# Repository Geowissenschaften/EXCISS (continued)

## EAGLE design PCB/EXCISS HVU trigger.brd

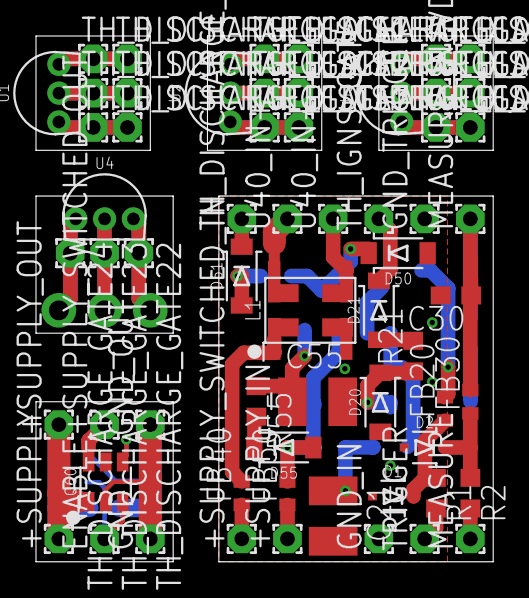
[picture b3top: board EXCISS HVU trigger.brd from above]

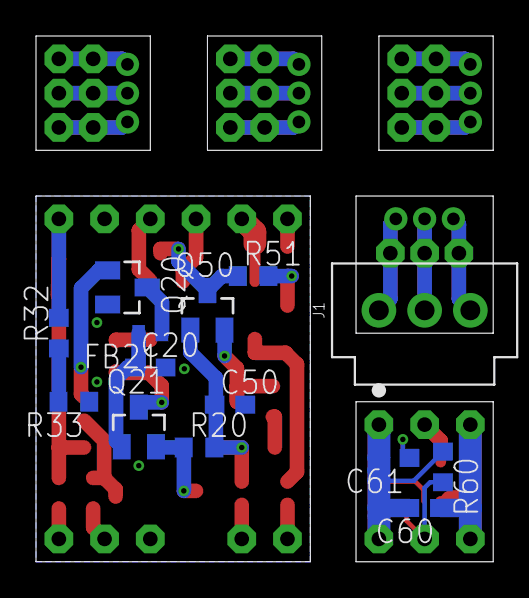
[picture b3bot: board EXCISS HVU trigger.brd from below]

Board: 2 copper layers, 25.4 x 29.2 mm, 76 parts (14 on the bottom side), 42 nets.

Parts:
+SUPPLY: WIREPAD1,6/0,8; 1,6/0,8
+SUPPLY_IN: WIREPAD1,6/0,8; 1,6/0,8
+SUPPLY_OUT: WIREPAD1,6/0,8; 1,6/0,8
+SUPPLY_SWITCHED_IN: WIREPAD1,6/0,8; 1,6/0,8
+SUPPLY_SWITCHED_OUT: WIREPAD1,6/0,8; 1,6/0,8
C20, C30, C50: 2,2nF; C0603
C21, C55: 47µF; C1210
C60: 1µF; C0603
C61: 10nF; C0603
D1, D2: SP4020-01FTG; SOD-323
D20, D21, D50, D51, D55: SL1M; SOD-123FL
ENABLE: WIREPAD1,6/0,8; 1,6/0,8
FB20, FB21, FB30, FB40, FB50: BLM18PG471SN1D; 0402
GND: WIREPAD1,6/0,8; 1,6/0,8
GND_IN: WIREPAD1,6/0,8; 1,6/0,8
GND_OUT: WIREPAD1,6/0,8; 1,6/0,8
GND_TRIGGER: WIREPAD1,6/0,8; 1,6/0,8
J1: 70543-0002; MOLEX_70543-0002
L1: DLW5ATN272SQ2; DLW5AT
MEASURE: WIREPAD1,6/0,8; 1,6/0,8
MEASURE_IN_VD: WIREPAD1,6/0,8; 1,6/0,8
Q20: PDTC143ZT; SOT23-3
Q21, Q50: PDTB123TT; SOT23-3
Q60: TPS22810DBV; SOT23-6_DBV
R1, R2: 100R; R0603
R20, R55: 4,7K; R0603
R21, R51: 180R; R0603
R32: 22K; R0603
R33: 3,9K; R0603
R60: 10K; R0603
TH_DISCHARGE_GATE, TH_DISCHARGE_GATE1, TH_DISCHARGE_GATE2, TH_DISCHARGE_GATE3, TH_DISCHARGE_GATE4, TH_DISCHARGE_GATE5, TH_DISCHARGE_GATE6, TH_DISCHARGE_GATE7, TH_DISCHARGE_GATE8, TH_DISCHARGE_GATE9, TH_DISCHARGE_GATE10, TH_DISCHARGE_GATE11, TH_DISCHARGE_GATE12, TH_DISCHARGE_GATE13, TH_DISCHARGE_GATE14, TH_DISCHARGE_GATE15, TH_DISCHARGE_GATE16, TH_DISCHARGE_GATE17, TH_DISCHARGE_GATE18, TH_DISCHARGE_GATE22, TH_DISCHARGE_GATE23, TH_DISCHARGE_GATE24: WIREPAD1,6/0,8; 1,6/0,8
TH_IGNS_GATE: WIREPAD1,6/0,8; 1,6/0,8
TRIGGER: WIREPAD1,6/0,8; 1,6/0,8
U1, U2, U3, U4: DS18B20+; TO-92-STRAIGHT
U40_IN+, U40_IN-: WIREPAD1,6/0,8; 1,6/0,8

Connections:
+HVU_SUPPLY_SWITCHED_FB: FB40.2, L1.1A, L1.1B+
+SUPPLY: +SUPPLY_IN.1, FB50.1
+SUPPLY$1: +SUPPLY.1, +SUPPLY_OUT.1, C60.1, Q60.1
+SUPPLY_FB: C50.1, D55.A, FB50.2, Q50.1, R20.2
+SUPPLY_SWITCHED: +SUPPLY_SWITCHED_IN.1, FB40.1
+SUPPLY_SWITCHED$1: +SUPPLY_SWITCHED_OUT.1, Q60.6
AGND: C20.2, C21.2, C30.2, C50.2, C55.2, D1.A, D2.A, D20.A, D50.A, GND_IN.1, GND_TRIGGER.1, L1.4A, L1.4B, Q20.2, R33.1
ENABLE: ENABLE.1, Q60.3, R60.2
GND: C60.2, C61.2, GND.1, GND_OUT.1, Q60.2, R60.1
MEASURE: D2.C, FB30.1, R2.1
MEASURE_FB: C30.1, FB30.2, MEASURE_IN_VD.1, R32.2
unnamed: MEASURE.1, R2.2
unnamed: D20.C, Q21.3, R21.1
unnamed: D21.C, TH_IGNS_GATE.1
unnamed: R32.1, R33.2
unnamed: R1.2, TRIGGER.1
unnamed: TH_DISCHARGE_GATE1.1, TH_DISCHARGE_GATE4.1, U1.3
unnamed: C21.1, Q21.2, R20.1
unnamed: TH_DISCHARGE_GATE2.1, TH_DISCHARGE_GATE5.1, U1.2
unnamed: D21.A, R21.2
unnamed: TH_DISCHARGE_GATE3.1, TH_DISCHARGE_GATE6.1, U1.1
unnamed: L1.3A, L1.3B, U40_IN-.1
unnamed: TH_DISCHARGE_GATE7.1, TH_DISCHARGE_GATE10.1, U2.3
unnamed: C20.1, FB21.2, Q21.1
unnamed: C61.1, Q60.4
unnamed: D51.C, TH_DISCHARGE_GATE.1
unnamed: TH_DISCHARGE_GATE8.1, TH_DISCHARGE_GATE11.1, U2.2
unnamed: TH_DISCHARGE_GATE9.1, TH_DISCHARGE_GATE12.1, U2.1
unnamed: FB21.1, Q20.3
unnamed: TH_DISCHARGE_GATE13.1, TH_DISCHARGE_GATE16.1, U3.3
unnamed: D51.A, R51.2
unnamed: L1.2A, L1.2B, U40_IN+.1
unnamed: TH_DISCHARGE_GATE14.1, TH_DISCHARGE_GATE17.1, U3.2
unnamed: D50.C, Q50.3, R51.1
unnamed: C55.1, Q50.2, R55.1
unnamed: D55.C, R55.2
unnamed: TH_DISCHARGE_GATE15.1, TH_DISCHARGE_GATE18.1, U3.1
unnamed: J1.1, TH_DISCHARGE_GATE22.1, U4.3
unnamed: J1.2, TH_DISCHARGE_GATE23.1, U4.2
unnamed: J1.3, TH_DISCHARGE_GATE24.1, U4.1
TRIGGER: D1.C, FB20.1, R1.1
TRIGGER_FB: FB20.2, Q20.1

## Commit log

2019-06-11 circuit diagrams and PCB design files
2019-06-12 gitignore
    hidden files from mac os should be ignored
2019-06-12 firmware inital commit
2019-06-17 Initial upload of SCU firmware.
2019-06-17 Remove backups, add empty dirs.
2021-05-23 mechanical design release
